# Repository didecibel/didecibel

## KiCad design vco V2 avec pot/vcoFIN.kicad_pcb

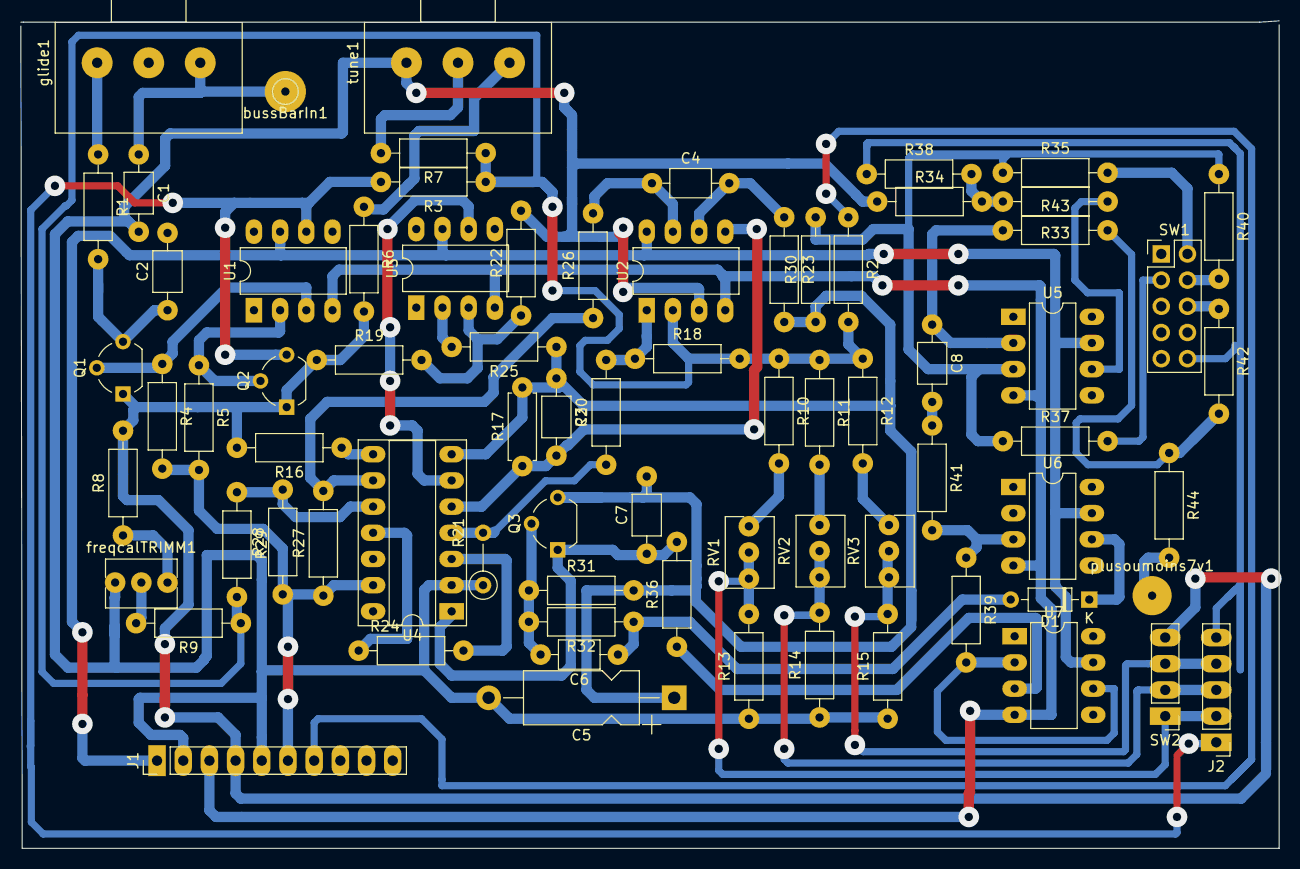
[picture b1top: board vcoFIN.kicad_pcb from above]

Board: 2 copper layers, 122.0 x 80.3 mm, 75 parts (0 on the bottom side), 56 nets.

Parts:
C1: 0.47u; C_Axial_L3.8mm_D2.6mm_P7.50mm_Horizontal
C2: 1u; C_Axial_L3.8mm_D2.6mm_P7.50mm_Horizontal
C3, C6, C7, C8: C; C_Axial_L3.8mm_D2.6mm_P7.50mm_Horizontal
C4: 100pF; C_Axial_L3.8mm_D2.6mm_P7.50mm_Horizontal
C5: 22u; CP_Axial_L11.0mm_D5.0mm_P18.00mm_Horizontal
D1: 1N4148; D_DO-35_SOD27_P7.62mm_Horizontal
J1: Conn_01x10_MountingPin; PinHeader_1x10_P2.54mm_Vertical
J2: Conn_01x05_MountingPin; PinHeader_1x05_P2.54mm_Vertical
Q1, Q2: 2N5163; TO-92_Wide
Q3: BC307; TO-92_Wide
R1: 330R; R_Axial_DIN0207_L6.3mm_D2.5mm_P10.16mm_Horizontal
R2: 330k; R_Axial_DIN0207_L6.3mm_D2.5mm_P10.16mm_Horizontal
R3: 27k; R_Axial_DIN0207_L6.3mm_D2.5mm_P10.16mm_Horizontal
R4, R5: 47k; R_Axial_DIN0207_L6.3mm_D2.5mm_P10.16mm_Horizontal
R6, R9: 100k; R_Axial_DIN0207_L6.3mm_D2.5mm_P10.16mm_Horizontal
R7: 270k; R_Axial_DIN0207_L6.3mm_D2.5mm_P10.16mm_Horizontal
R8: 30k; R_Axial_DIN0207_L6.3mm_D2.5mm_P10.16mm_Horizontal
R10: 360k; R_Axial_DIN0207_L6.3mm_D2.5mm_P10.16mm_Horizontal
R11: 180k; R_Axial_DIN0207_L6.3mm_D2.5mm_P10.16mm_Horizontal
R12: 130k; R_Axial_DIN0207_L6.3mm_D2.5mm_P10.16mm_Horizontal
R13, R14, R15: 1k; R_Axial_DIN0207_L6.3mm_D2.5mm_P10.16mm_Horizontal
R16: 100R; R_Axial_DIN0207_L6.3mm_D2.5mm_P10.16mm_Horizontal
R17: R_US; R_Axial_DIN0207_L6.3mm_D2.5mm_P7.62mm_Horizontal
R18, R19, R20, R22, R23: 20k; R_Axial_DIN0207_L6.3mm_D2.5mm_P10.16mm_Horizontal
R21: 1k tempco; R_Axial_DIN0207_L6.3mm_D2.5mm_P5.08mm_Vertical
R24, R26, R27, R28, R29, R30, R31, R32, R33, R34, R35, R36, R37, R38, R39, R40, R41, R42, R43, R44: R_US; R_Axial_DIN0207_L6.3mm_D2.5mm_P10.16mm_Horizontal
R25: 22k; R_Axial_DIN0207_L6.3mm_D2.5mm_P10.16mm_Horizontal
RV1, RV2, RV3: 50k; Potentiometer_Bourns_3266Y_Vertical
SW1: SW_Rotary2x4; PinHeader_2x05_P2.54mm_Vertical
SW2: SW_DP3Tbis; PinHeader_1x04_P2.54mm_Vertical
U1, U3, U5, U6, U7: TL071; DIP-8_W7.62mm_LongPads
U2: TL072; DIP-8_W7.62mm_LongPads
U4: CA3086; DIP-14_W7.62mm_Socket_LongPads
bussBarIn1: MountingHole_Pad; Pin_D1.0mm_L10.0mm
freqcalTRIMM1: 10k; Potentiometer_Bourns_3266Y_Vertical
glide1: 1M log; Potentiometer_Alps_RK163_Single_Horizontal
plusoumoins7v1: MountingHole_Pad; MountingHole_2.2mm_M2_DIN965_Pad
tune1: 10k lin; Potentiometer_Alps_RK163_Single_Horizontal

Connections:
+3V8: C3.1, C5.1, C7.2, Q3.3, R17.2, R23.2, R25.1, R30.1, R31.2, U4.7
+7.5V: J1.4, Q1.1, Q2.1, R6.2, R8.2, R16.2, R19.1, SW2.4
+15V: J1.1, U1.7, U2.8, U3.7, U5.7, U6.7, U7.7
-8V: J1.6, R4.2, R5.2, R27.1, R28.1, U4.13
-15V: J1.3, U1.4, U2.4, U3.4, U5.4, U6.4, U7.4
GND: C1.2, C2.2, C5.2, J1.2, J1.5, R13.1, R14.1, R15.1, R21.1, R22.2, R34.1, SW1.5, U2.3, U4.2, freqcalTRIMM1.3, tune1.3
unnamed: C1.1, bussBarIn1.1, glide1.1
unnamed: C2.1, Q1.3, R1.2
unnamed: C3.2, R17.1, U2.5, U4.5
unnamed: C4.1, R26.2, U2.7
unnamed: C4.2, R23.1, U2.6
unnamed: C6.1, D1.2, R32.1
unnamed: C6.2, Q3.2, R31.1, R32.2
unnamed: C7.1, Q3.1, R36.2, U4.1
unnamed: C8.1, R43.1, U5.2
unnamed: C8.2, R41.1
unnamed: D1.1, U6.6
unnamed: J1.7, R2.1
unnamed: J2.1, Q2.3, R3.2, U1.6
unnamed: J2.2, R13.2, RV1.2, RV1.3, SW2.1
unnamed: J2.3, R14.2, RV2.2, RV2.3, SW2.2
unnamed: J2.4, R15.2, RV3.2, RV3.3, SW2.3
unnamed: J2.5, R38.1, SW1.10
unnamed: Q1.2, R4.1, U1.3
unnamed: Q2.2, R5.1, U1.2
unnamed: R1.1, glide1.3
unnamed: R6.1, tune1.1
unnamed: R7.2, tune1.2
unnamed: R8.1, freqcalTRIMM1.1
unnamed: R9.2, freqcalTRIMM1.2
unnamed: R2.2, R3.1, R7.1, R9.1, R10.1, R11.1, R12.1, R18.2, R29.2, U2.2
unnamed: R10.2, RV1.1
unnamed: R11.2, RV2.1
unnamed: R12.2, RV3.1
unnamed: R16.1, U4.8
unnamed: R18.1, R20.2, U2.1
unnamed: R19.2, R22.1, U3.3
unnamed: R20.1, R21.2, U4.4
unnamed: R24.1, U4.11
unnamed: R24.2, U4.3
unnamed: R25.2, U3.2
unnamed: R26.1, R27.2, U4.9
unnamed: R28.2, R29.1, U4.10
unnamed: R30.2, R35.1, R37.1, R40.1, U5.3
unnamed: R33.1, U5.6
unnamed: R33.2, R34.2, R38.2
unnamed: R35.2, SW1.2
unnamed: R36.1, U7.3
unnamed: R37.2, SW1.3
unnamed: R39.1, R41.2, U6.3
unnamed: R39.2, U7.2, U7.6
unnamed: R40.2, SW1.4
unnamed: R42.1, SW1.6
unnamed: R42.2, R43.2, R44.1
unnamed: R44.2, plusoumoins7v1.1
unnamed: U3.6, U4.6

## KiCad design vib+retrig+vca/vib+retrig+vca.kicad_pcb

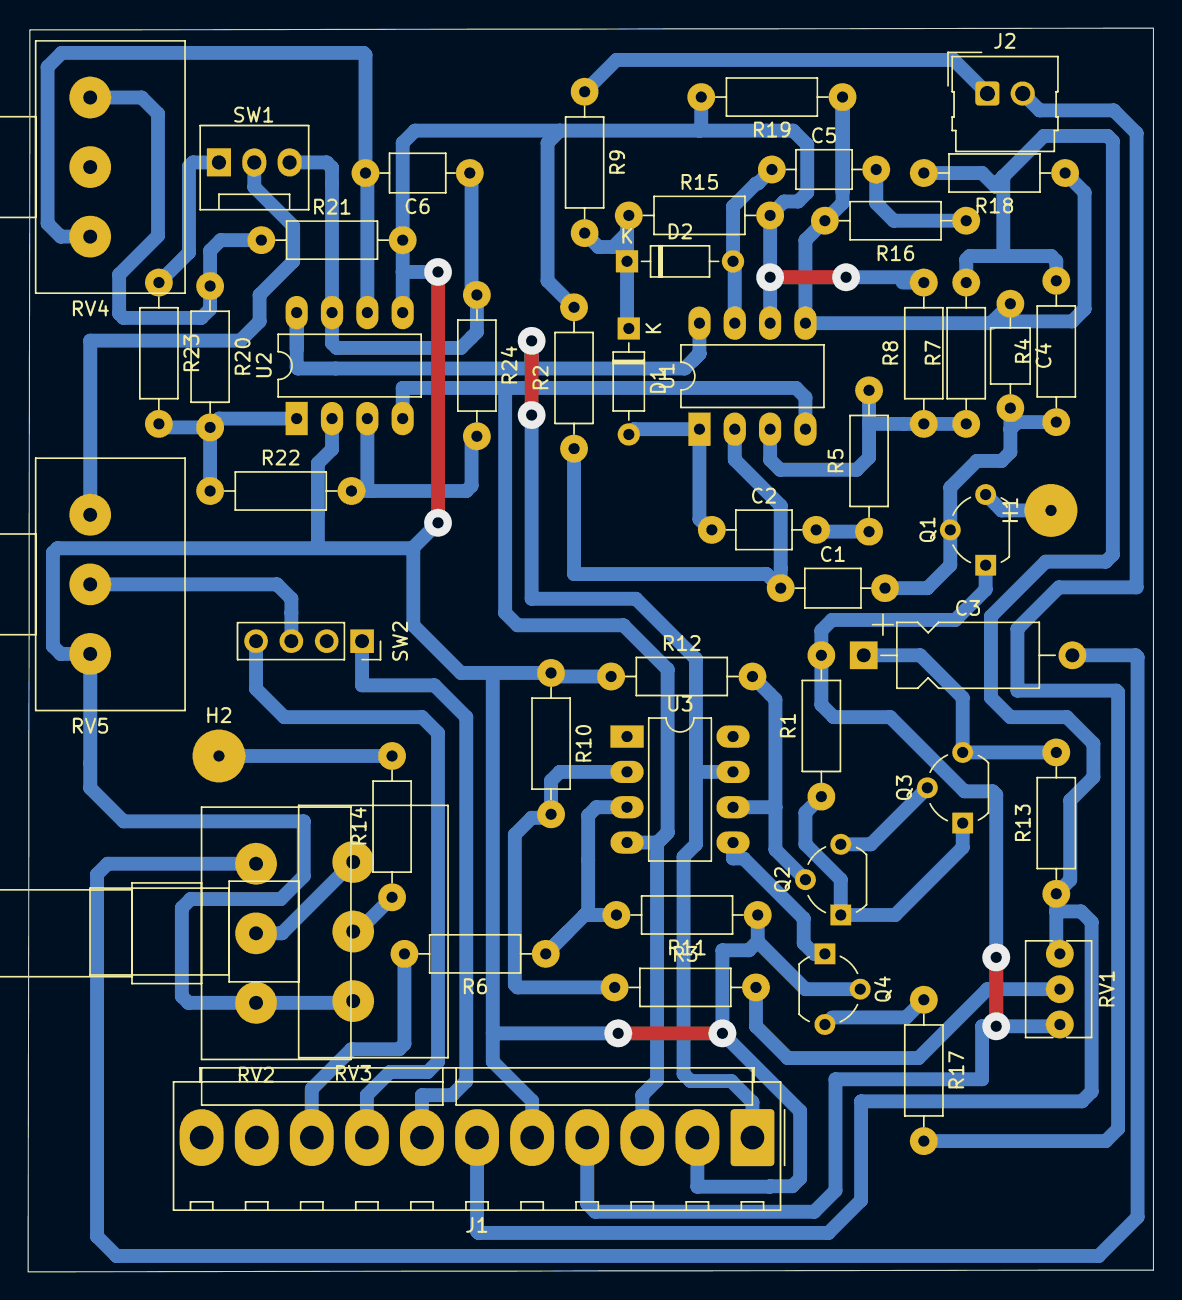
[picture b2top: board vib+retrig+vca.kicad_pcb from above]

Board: 2 copper layers, 80.9 x 89.4 mm, 50 parts (0 on the bottom side), 41 nets.

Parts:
C1, C2, C4, C5, C6: C; C_Axial_L3.8mm_D2.6mm_P7.50mm_Horizontal
C3: C_Polarized; CP_Axial_L10.0mm_D4.5mm_P15.00mm_Horizontal
D1, D2: 1N4148; D_DO-35_SOD27_P7.62mm_Horizontal
H1, H2: MountingHole_Pad; MountingHole_2.2mm_M2_DIN965_Pad
J1: Conn_01x10_MountingPin; Molex_KK-396_A-41791-0011_1x11_P3.96mm_Vertical
J2: Conn_01x02_MountingPin; Molex_SL_171971-0002_1x02_P2.54mm_Vertical
Q1: Q_NJFET_DSG; TO-92L_Wide
Q2, Q3: BC237; TO-92_Wide
Q4: BC307; TO-92_Wide
R1, R2, R3, R4, R5, R6, R7, R8, R9, R10, R11, R12, R13, R14, R15, R16, R17, R18, R19, R20, R21, R22, R23, R24: R_US; R_Axial_DIN0207_L6.3mm_D2.5mm_P10.16mm_Horizontal
RV1: R_Potentiometer_Trim; Potentiometer_Bourns_3266Y_Vertical
RV2, RV3, RV4, RV5: R_Potentiometer; Potentiometer_Alps_RK163_Single_Horizontal
SW1: SW_SPDT; FanPinHeader_1x03_P2.54mm_Vertical
SW2: SW_SP3T; PinSocket_1x04_P2.54mm_Vertical
U1, U2: TL072; DIP-8_W7.62mm_LongPads
U3: CA3080; DIP-8_W7.62mm_LongPads

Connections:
+7.5V: J1.4, Q1.1, R1.2, RV1.1
+15V: J1.1, U1.8, U2.8, U3.7
-8V: J1.6, R4.2, R7.2, R13.1, R18.2, RV1.3
-15V: J1.3, U1.4, U2.4, U3.4
GND: J1.2, J1.5, Q4.2, R2.2, R8.2, R10.1, R11.1, R12.1, R15.2, R19.2, R21.2, RV2.3, RV3.3, RV5.3, U1.6, U2.2, U2.5
unnamed: C1.1, R2.1, U1.2
unnamed: C1.2, C4.2, Q1.2, R4.1
unnamed: C2.1, D1.2, U1.1
unnamed: C2.2, R5.1
unnamed: C3.1, Q3.3, R13.2
unnamed: C3.2, RV2.1
unnamed: C4.1, R16.2, R18.1, R19.1, U1.5
unnamed: C5.1, D2.2, U1.7
unnamed: C5.2, R16.1
unnamed: C6.1, R24.1, SW1.3, U2.7
unnamed: C6.2, RV4.3, U2.6
unnamed: D1.1, D2.1, R9.2, R15.1
unnamed: H1.1, Q1.3
unnamed: H2.1, R14.2
unnamed: J1.7, SW2.1
unnamed: J1.8, SW2.4
unnamed: J1.9, R6.2
unnamed: J2.1, R9.1
unnamed: J2.2, R17.2
unnamed: Q2.1, Q3.1, R1.1
unnamed: Q2.2, R12.2, U3.6
unnamed: Q2.3, Q3.2
unnamed: Q4.1, U3.5
unnamed: Q4.3, R17.1
unnamed: R3.2, RV1.2
unnamed: R5.2, R7.1, R8.1, U1.3
unnamed: R3.1, R10.2, U3.2
unnamed: R6.1, R11.2, U3.3
unnamed: R14.1, RV3.2
unnamed: R20.1, R21.1, RV4.1
unnamed: R20.2, R22.1, R23.2, U2.1
unnamed: R22.2, R24.2, U2.3
unnamed: R23.1, SW1.1
unnamed: RV2.2, RV3.1
unnamed: RV5.1, SW1.2
unnamed: RV5.2, SW2.3

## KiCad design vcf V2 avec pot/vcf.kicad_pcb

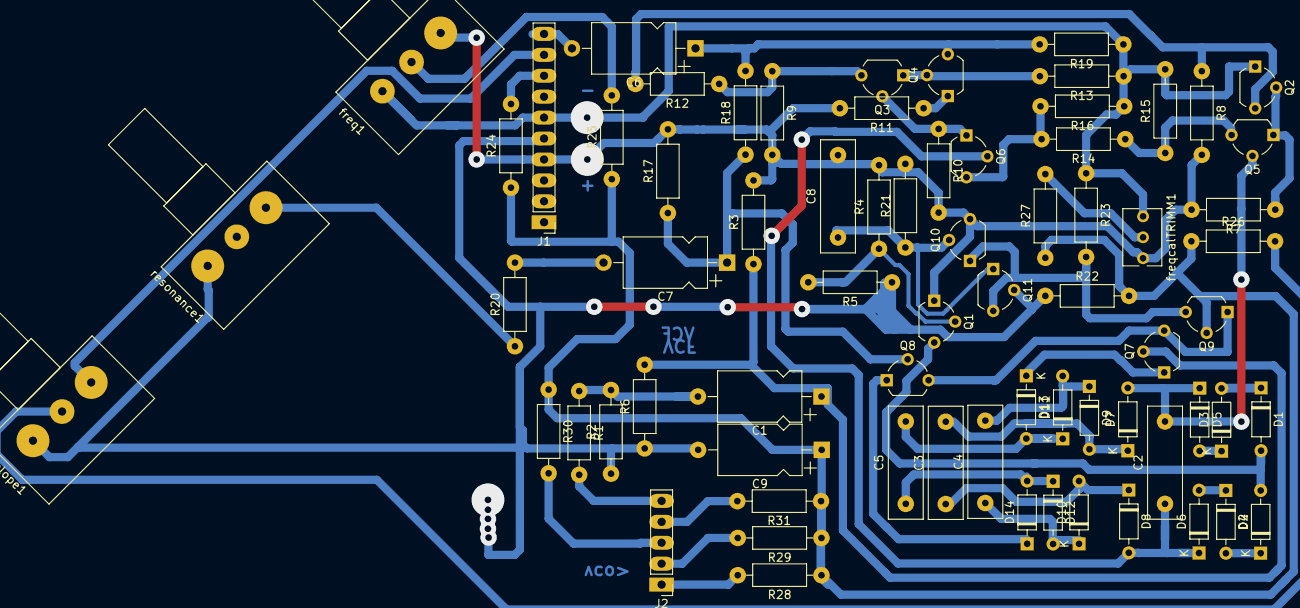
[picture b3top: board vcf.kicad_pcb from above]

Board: 2 copper layers, 71 parts (0 on the bottom side), 48 nets.

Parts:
C1, C6, C7, C9: C_Polarized; CP_Axial_L10.0mm_D6.0mm_P15.00mm_Horizontal
C2, C3, C4, C5, C8: C; C_Rect_L13.5mm_W4.0mm_P10.00mm_FKS3_FKP3_MKS4
D1, D2, D3, D4, D5, D6, D7, D8, D9, D10, D11, D12, D13, D14: 1N4148; D_DO-35_SOD27_P7.62mm_Horizontal
J1: Conn_01x10_MountingPin; PinHeader_1x10_P2.54mm_Vertical
J2: Conn_01x05_MountingPin; PinHeader_1x05_P2.54mm_Vertical
Q1, Q2, Q3, Q4, Q5, Q6, Q7, Q8, Q9, Q11: BC237; TO-92_Wide
Q10: BC307; TO-92_Wide
R1, R2, R3, R4, R5, R6, R7, R8, R9, R10, R11, R12, R13, R14, R15, R16, R17, R18, R19, R20, R21, R22, R23, R24, R25, R26, R27, R28, R29, R30, R31: R_US; R_Axial_DIN0207_L6.3mm_D2.5mm_P10.16mm_Horizontal
envelope1: R_Potentiometer; Potentiometer_Alps_RK163_Single_Horizontal
freq1: R_Potentiometer; Potentiometer_Alps_RK163_Single_Horizontal
freqcalTRIMM1: R_Potentiometer_Trim; Potentiometer_Bourns_3266Y_Vertical
resonance1: R_Potentiometer; Potentiometer_Alps_RK163_Single_Horizontal

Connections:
+7.5V: C8.2, J1.4, Q1.1, Q10.3, R3.2, R4.2, R7.2, R8.2, R9.2, R10.2, R11.2, R17.2, R21.2, freq1.1, freqcalTRIMM1.1
-8V: J1.6, Q2.1, R13.1, R15.2, R16.1, R19.1, R23.1, freq1.3, freqcalTRIMM1.3
GND: C9.2, J1.5, Q11.2, R2.1, R5.1, R6.1, R22.1, envelope1.3, resonance1.3
unnamed: C1.1, Q7.2, R3.1, R6.2
unnamed: C1.2, R1.1, R2.2
unnamed: C2.1, D6.1, D8.2, Q6.2
unnamed: C2.2, D5.1, D7.2, Q5.2
unnamed: C3.1, D8.1, D10.2
unnamed: C3.2, D7.1, D9.2
unnamed: C4.1, D10.1, D12.2
unnamed: C4.2, D9.1, D11.2
unnamed: C5.1, D12.1, D14.2
unnamed: C5.2, D11.1, D13.2
unnamed: C6.1, Q4.3, R18.2, R19.2
unnamed: C6.2, J1.10
unnamed: C7.1, Q8.2, R17.1, R18.1
unnamed: C7.2, R20.2
unnamed: C8.1, Q10.2, Q11.1, R21.1
unnamed: C9.1, Q9.2, R22.2, R24.1, R25.1, R26.1, R27.1, R28.1, R29.1, R30.1, R31.1
unnamed: D1.1, D3.2
unnamed: D1.2, D2.2, Q1.3
unnamed: D2.1, D4.2
unnamed: D3.1, D5.2
unnamed: D4.1, D6.2
unnamed: D13.1, Q7.1
unnamed: D14.1, Q8.1
unnamed: J1.8, R24.2
unnamed: J1.9, envelope1.1
unnamed: J2.1, R28.2
unnamed: J2.2, R29.2
unnamed: J2.3, R30.2
unnamed: J2.4, R31.2
unnamed: J2.5, R1.2
unnamed: Q1.2, R4.1, R5.2
unnamed: Q2.2, Q5.1, R7.1
unnamed: Q2.3, R8.1, R12.2
unnamed: Q3.1, Q4.2, R13.2
unnamed: Q3.2, Q6.1, R10.1
unnamed: Q3.3, R9.1, R12.1
unnamed: Q4.1, R11.1
unnamed: Q5.3, R14.1, R15.1
unnamed: Q6.3, R14.2, R16.2
unnamed: Q7.3, Q8.3, Q9.1
unnamed: Q9.3, Q10.1, Q11.3, R23.2
unnamed: R20.1, resonance1.1
unnamed: R25.2, freq1.2
unnamed: R26.2, envelope1.2
unnamed: R27.2, freqcalTRIMM1.2

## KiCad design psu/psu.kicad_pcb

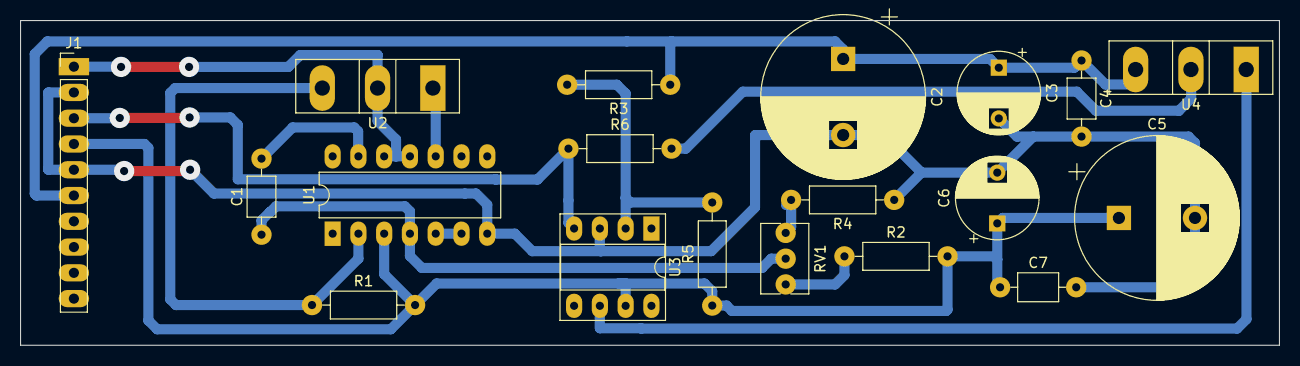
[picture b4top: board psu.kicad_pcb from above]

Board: 2 copper layers, 124.1 x 32.0 mm, 19 parts (0 on the bottom side), 15 nets.

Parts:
C1: 470p; C_Axial_L3.8mm_D2.6mm_P7.50mm_Horizontal
C2, C5: 470u; CP_Radial_D16.0mm_P7.50mm
C3, C6: 10u; CP_Radial_D8.0mm_P5.00mm
C4: 0.1u; C_Axial_L3.8mm_D2.6mm_P7.50mm_Horizontal
C7: 0.1; C_Axial_L3.8mm_D2.6mm_P7.50mm_Horizontal
J1: Conn_01x10_MountingPin; PinHeader_1x10_P2.54mm_Vertical
R1: 10R; R_Axial_DIN0207_L6.3mm_D2.5mm_P10.16mm_Horizontal
R2: 220R; R_Axial_DIN0207_L6.3mm_D2.5mm_P10.16mm_Horizontal
R3, R4, R5: 10k; R_Axial_DIN0207_L6.3mm_D2.5mm_P10.16mm_Horizontal
R6: 33R; R_Axial_DIN0207_L6.3mm_D2.5mm_P10.16mm_Horizontal
RV1: 470R; Potentiometer_Bourns_3266Y_Vertical
U1: LM723; DIP-14_W7.62mm_LongPads
U2: BDX53; TO-247-3_Vertical
U3: TL071; DIP-8_W7.62mm_Socket_LongPads
U4: BDX54; TO-247-3_Vertical

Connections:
+7.5V: C5.1, C6.1, C7.1, J1.4, R1.2, R2.2, R5.1, U1.3, U3.7
+15V: J1.1, U1.11, U1.12, U2.2
-8V: C2.1, C3.1, C4.1, J1.6, R3.1, U4.3
-15V: J1.3, R6.1, U3.4
GND: C2.2, C3.2, C4.2, C5.2, C6.2, C7.2, J1.2, J1.5, R4.1, U1.7, U3.3
unnamed: C1.1, RV1.2, U1.4
unnamed: C1.2, U1.13
unnamed: R1.1, U1.2, U2.3
unnamed: R2.1, RV1.1
unnamed: R3.2, R5.2, U3.2
unnamed: R4.2, RV1.3
unnamed: R6.2, U4.2
unnamed: U1.5, U1.6
unnamed: U1.10, U2.1
unnamed: U3.6, U4.1

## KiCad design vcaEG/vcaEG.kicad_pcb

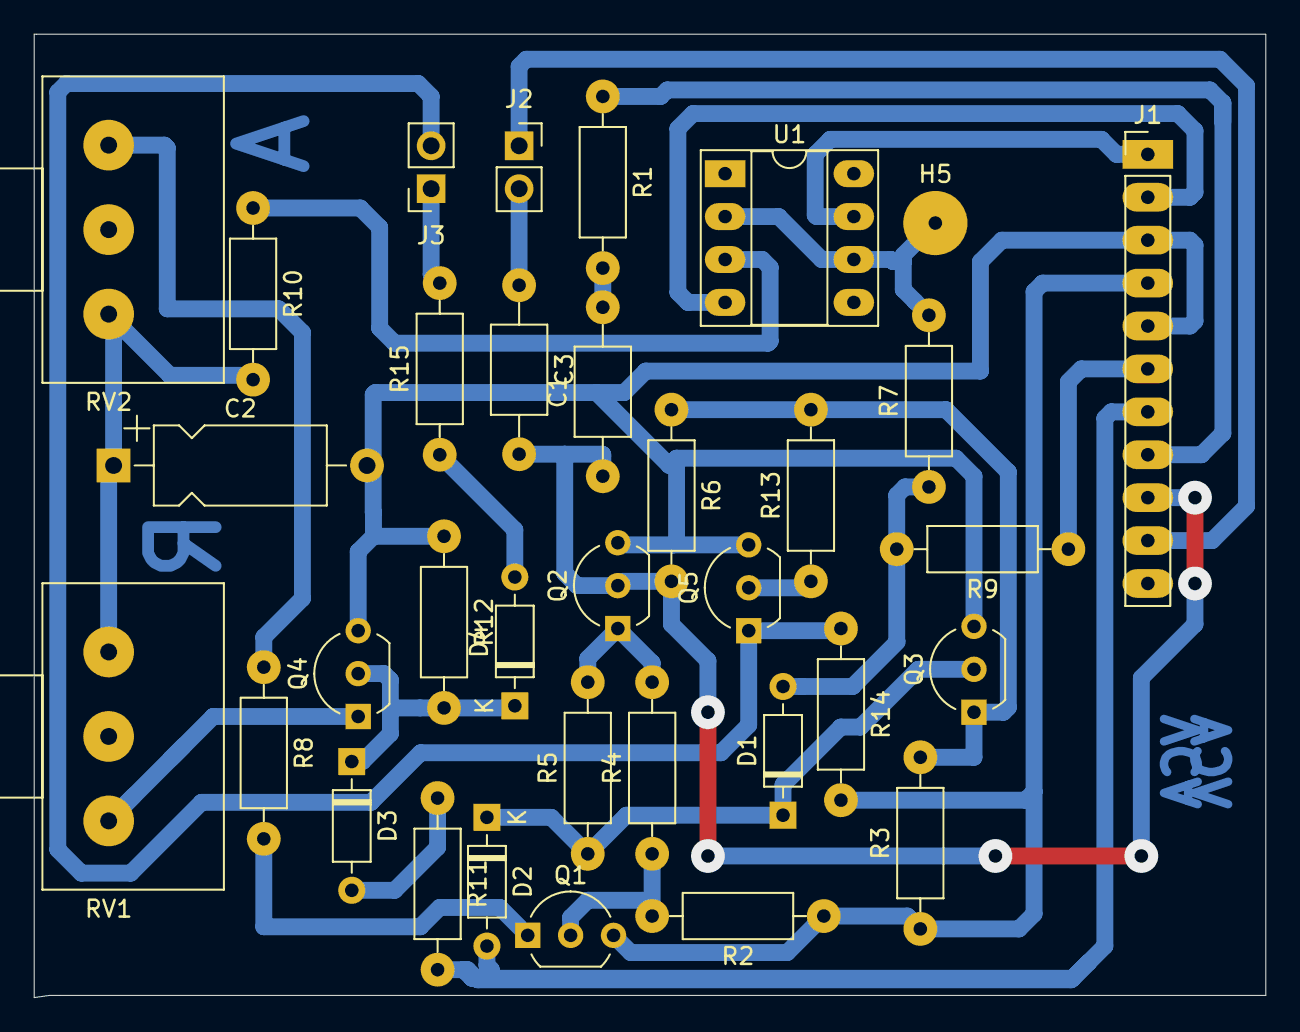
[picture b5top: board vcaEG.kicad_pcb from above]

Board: 2 copper layers, 72.9 x 57.0 mm, 34 parts (0 on the bottom side), 28 nets.

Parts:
C1, C3: C; C_Axial_L5.1mm_D3.1mm_P10.00mm_Horizontal
C2: C_Polarized; CP_Axial_L10.0mm_D4.5mm_P15.00mm_Horizontal
D1, D2, D3, D4: 1N4148; D_DO-35_SOD27_P7.62mm_Horizontal
H5: MountingHole_Pad; MountingHole_2.2mm_M2_DIN965_Pad
J1: Conn_01x10_MountingPin; PinHeader_1x11_P2.54mm_Vertical
J2, J3: Conn_01x02_MountingPin; PinSocket_1x02_P2.54mm_Vertical
Q1: BC307; TO-92_Inline_Wide
Q2, Q3, Q4, Q5: BC237; TO-92_Inline_Wide
R1, R2, R3, R4, R5, R6, R7, R8, R9, R10, R11, R12, R13, R14, R15: R_US; R_Axial_DIN0207_L6.3mm_D2.5mm_P10.16mm_Horizontal
RV1, RV2: R_Potentiometer; Potentiometer_Alps_RK163_Single_Horizontal
U1: TL071; DIP-8_W7.62mm_Socket_LongPads

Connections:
+7.5V: J1.4, Q1.3, R2.1, R3.1, R14.2
+15V: J1.1, U1.7
-8V: J1.6, R9.1
-15V: J1.2, U1.4
GND: C2.2, J1.3, J1.5, Q2.3, Q3.3, Q4.3, Q5.3, R12.1
unnamed: C1.1, C3.2, J1.9, Q2.2, R6.2
unnamed: C1.2, R1.2
unnamed: C2.1, R10.2, RV1.1, RV2.3
unnamed: C3.1, J2.2
unnamed: D1.1, D2.1, Q3.2, R5.1
unnamed: D1.2, R7.1, R9.2
unnamed: D2.2, J1.7, R11.2
unnamed: D3.1, D4.1, Q4.2, R12.2
unnamed: D3.2, R11.1
unnamed: D4.2, R15.1
unnamed: H5.1, R7.2, U1.2, U1.6
unnamed: J1.8, R1.1
unnamed: J1.10, J2.1
unnamed: J3.1, R15.2
unnamed: J3.2, Q5.1, R14.1
unnamed: Q1.1, R8.2
unnamed: Q1.2, R2.2, R4.1
unnamed: Q2.1, R4.2, R5.2
unnamed: Q3.1, R3.2, R6.1, R13.2
unnamed: Q4.1, RV1.3
unnamed: Q5.2, R13.1
unnamed: R8.1, RV2.1
unnamed: R10.1, U1.3
